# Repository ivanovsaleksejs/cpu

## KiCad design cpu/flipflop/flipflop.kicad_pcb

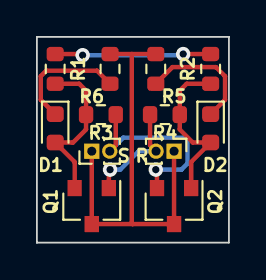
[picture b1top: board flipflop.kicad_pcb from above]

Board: 2 copper layers, 10.7 x 11.4 mm, 12 parts (0 on the bottom side), 8 nets.

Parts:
D1: LED RED; LED_0603_1608Metric
D2: LED GREEN; LED_0603_1608Metric
Q1: BCX56; SOT-23
Q2: BC547; SOT-23
R: S; PinHeader_1x02_P1.00mm_Vertical
R1, R2: 1k; R_0603_1608Metric
R3, R4, R5, R6: 10k; R_0603_1608Metric
S: R; PinHeader_1x02_P1.00mm_Vertical

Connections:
+5V: R1.1, R2.1
-5V: D2.1, R6.1
unnamed: D1.1, R5.2
unnamed: D1.2, Q1.2, R1.2, R3.2
unnamed: D2.2, Q2.1, R2.2, R4.1
unnamed: Q1.1, R.2, R4.2
unnamed: Q1.3, Q2.3, R.1, R5.1, R6.2, S.1
unnamed: Q2.2, R3.1, S.2

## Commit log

2021-09-05 .gitignore
2021-09-05 Flipflop v0.1
2021-09-05 Added SVGs of schematic and board
2021-09-05 Rendered view of flipflop board
